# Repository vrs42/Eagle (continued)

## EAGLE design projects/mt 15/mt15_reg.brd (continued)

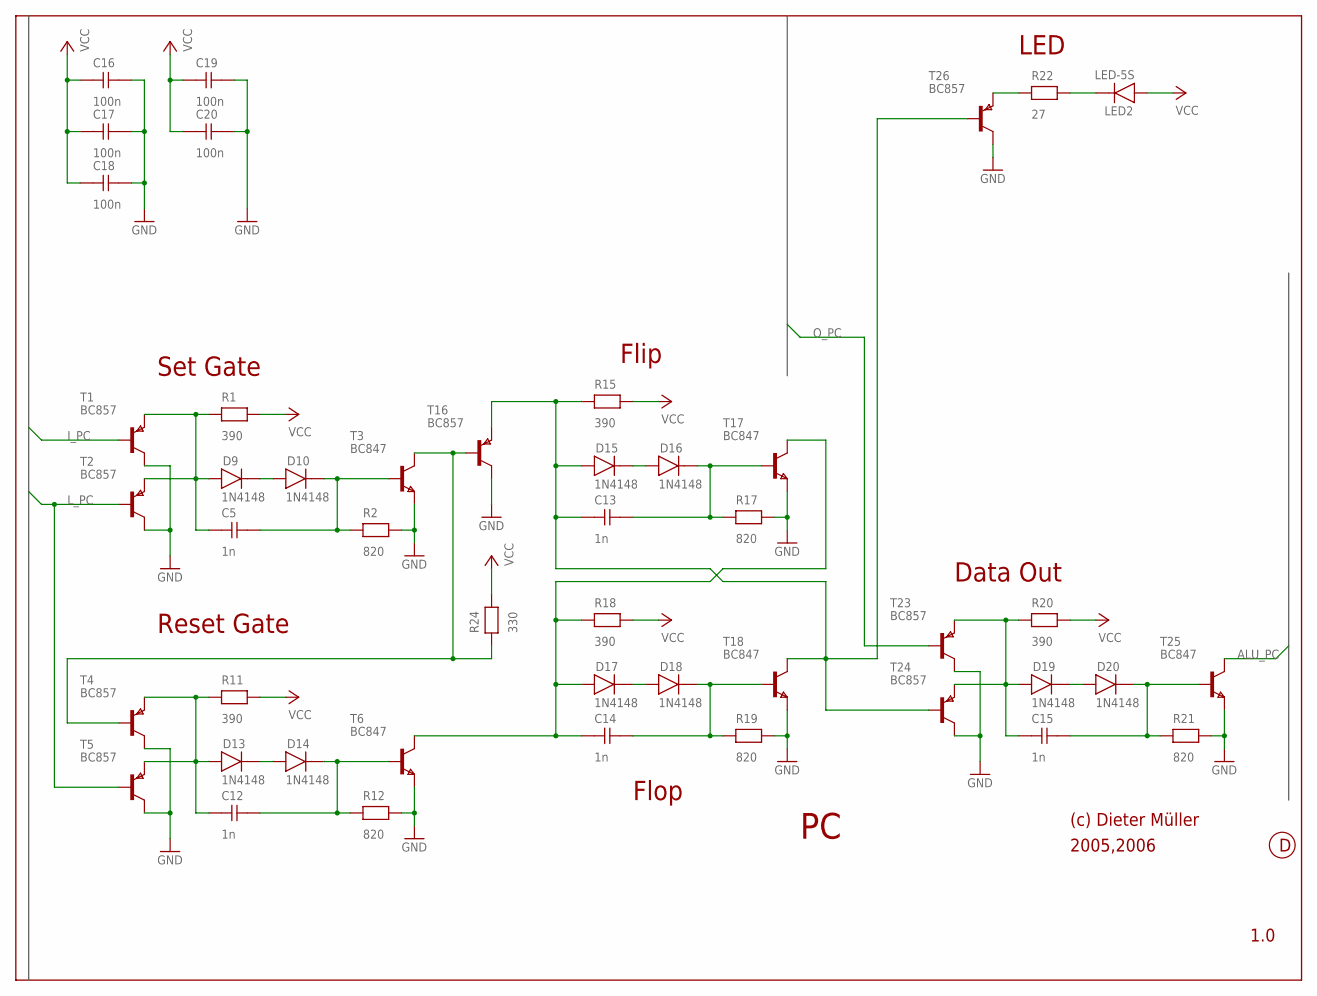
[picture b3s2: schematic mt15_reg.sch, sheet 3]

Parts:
C5, C12, C13, C14, C15: 1n; 0204
C16, C17, C18, C19, C20: 100n; 0204
D9, D10, D13, D14, D15, D16, D17, D18, D19, D20: 1N4148; 0204D
LED2: LED-5S
R1, R11, R15, R18, R20: 390; 0204
R2, R12, R17, R19, R21: 820; 0204
R22: 27; 0204
R24: 330; 0204
T1, T2, T4, T5, T16, T23, T24, T26: BC857; SOT-23
T3, T6, T17, T18, T25: BC847; SOT-23

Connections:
ALU_PC: T25.3 (C)
GND: C16.2, C17.2, C18.2, C19.2, C20.2, R2.2, R12.2, R17.2, R19.2, R21.2, T1.3 (C), T2.3 (C), T3.1 (E), T4.3 (C), T5.3 (C), T6.1 (E), T16.3 (C), T17.1 (E), T18.1 (E), T23.3 (C), T24.3 (C), T25.1 (E), T26.3 (C); also elsewhere on the board
I_PC: T1.2 (B)
L_PC: T2.2 (B), T5.2 (B)
unnamed: C5.1, D9.1 (A), R1.1, T1.1 (E), T2.1 (E)
unnamed: D9.2 (K), D10.1 (A)
unnamed: C5.2, D10.2 (K), R2.1, T3.2 (B)
unnamed: R24.1, T3.3 (C), T4.2 (B), T16.2 (B)
unnamed: C12.1, D13.1 (A), R11.1, T4.1 (E), T5.1 (E)
unnamed: D13.2 (K), D14.1 (A)
unnamed: C12.2, D14.2 (K), R12.1, T6.2 (B)
unnamed: D15.2 (K), D16.1 (A)
unnamed: C13.2, D16.2 (K), R17.1, T17.2 (B)
unnamed: D17.2 (K), D18.1 (A)
unnamed: C14.2, D18.2 (K), R19.1, T18.2 (B)
unnamed: C14.1, D17.1 (A), R18.1, T6.3 (C), T17.3 (C)
unnamed: C13.1, D15.1 (A), R15.1, T16.1 (E), T18.3 (C), T24.2 (B), T26.2 (B)
unnamed: C15.1, D19.1 (A), R20.1, T23.1 (E), T24.1 (E)
unnamed: D19.2 (K), D20.1 (A)
unnamed: C15.2, D20.2 (K), R21.1, T25.2 (B)
unnamed: R22.1, T26.1 (E)
unnamed: LED2.2 (K), R22.2
O_PC: T23.2 (B)
VCC: C16.1, C17.1, C18.1, C19.1, C20.1, LED2.1 (A), R1.2, R11.2, R15.2, R18.2, R20.2, R24.2; also elsewhere on the board

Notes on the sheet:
Set Gate
Reset Gate
Flip
Flop
Data Out
LED
(c) Dieter Müller
2005,2006
1.0

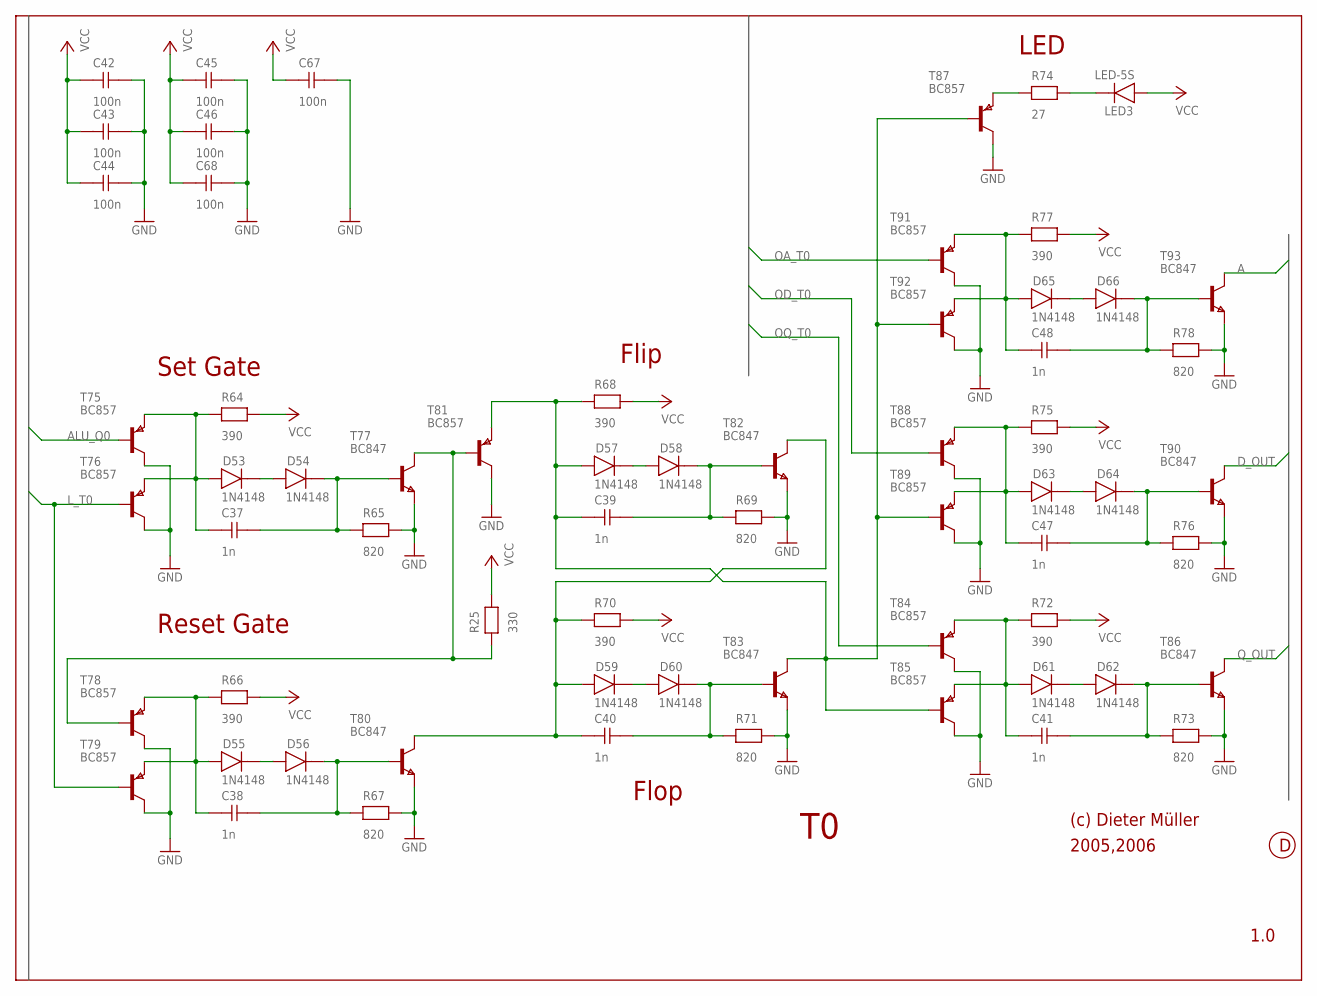
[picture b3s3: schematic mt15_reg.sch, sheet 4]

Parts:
C37, C38, C39, C40, C41, C47, C48: 1n; 0204
C42, C43, C44, C45, C46, C67, C68: 100n; 0204
D53, D54, D55, D56, D57, D58, D59, D60, D61, D62, D63, D64, D65, D66: 1N4148; 0204D
LED3: LED-5S
R25: 330; 0204
R64, R66, R68, R70, R72, R75, R77: 390; 0204
R65, R67, R69, R71, R73, R76, R78: 820; 0204
R74: 27; 0204
T75, T76, T78, T79, T81, T84, T85, T87, T88, T89, T91, T92: BC857; SOT-23
T77, T80, T82, T83, T86, T90, T93: BC847; SOT-23

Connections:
A: T93.3 (C); also elsewhere on the board
ALU_Q0: T75.2 (B)
D_OUT: T90.3 (C); also elsewhere on the board
GND: C42.2, C43.2, C44.2, C45.2, C46.2, C67.2, C68.2, R65.2, R67.2, R69.2, R71.2, R73.2, R76.2, R78.2, T75.3 (C), T76.3 (C), T77.1 (E), T78.3 (C), T79.3 (C), T80.1 (E), T81.3 (C), T82.1 (E), T83.1 (E), T84.3 (C), T85.3 (C), T86.1 (E), T87.3 (C), T88.3 (C), T89.3 (C), T90.1 (E), T91.3 (C), T92.3 (C), T93.1 (E); also elsewhere on the board
L_T0: T76.2 (B), T79.2 (B)
unnamed: C37.1, D53.1 (A), R64.1, T75.1 (E), T76.1 (E)
unnamed: D53.2 (K), D54.1 (A)
unnamed: C37.2, D54.2 (K), R65.1, T77.2 (B)
unnamed: R25.1, T77.3 (C), T78.2 (B), T81.2 (B)
unnamed: C38.1, D55.1 (A), R66.1, T78.1 (E), T79.1 (E)
unnamed: D55.2 (K), D56.1 (A)
unnamed: C38.2, D56.2 (K), R67.1, T80.2 (B)
unnamed: D57.2 (K), D58.1 (A)
unnamed: C39.2, D58.2 (K), R69.1, T82.2 (B)
unnamed: D59.2 (K), D60.1 (A)
unnamed: C40.2, D60.2 (K), R71.1, T83.2 (B)
unnamed: C40.1, D59.1 (A), R70.1, T80.3 (C), T82.3 (C)
unnamed: C39.1, D57.1 (A), R68.1, T81.1 (E), T83.3 (C), T85.2 (B), T87.2 (B), T89.2 (B), T92.2 (B)
unnamed: C41.1, D61.1 (A), R72.1, T84.1 (E), T85.1 (E)
unnamed: D61.2 (K), D62.1 (A)
unnamed: C41.2, D62.2 (K), R73.1, T86.2 (B)
unnamed: R74.1, T87.1 (E)
unnamed: LED3.2 (K), R74.2
unnamed: C47.1, D63.1 (A), R75.1, T88.1 (E), T89.1 (E)
unnamed: D63.2 (K), D64.1 (A)
unnamed: C47.2, D64.2 (K), R76.1, T90.2 (B)
unnamed: C48.1, D65.1 (A), R77.1, T91.1 (E), T92.1 (E)
unnamed: D65.2 (K), D66.1 (A)
unnamed: C48.2, D66.2 (K), R78.1, T93.2 (B)
OA_T0: T91.2 (B)
OD_T0: T88.2 (B)
OQ_T0: T84.2 (B)
Q_OUT: T86.3 (C); also elsewhere on the board
VCC: C42.1, C43.1, C44.1, C45.1, C46.1, C67.1, C68.1, LED3.1 (A), R25.2, R64.2, R66.2, R68.2, R70.2, R72.2, R75.2, R77.2; also elsewhere on the board

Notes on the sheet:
Set Gate
Reset Gate
Flip
Flop
LED
(c) Dieter Müller
2005,2006
1.0

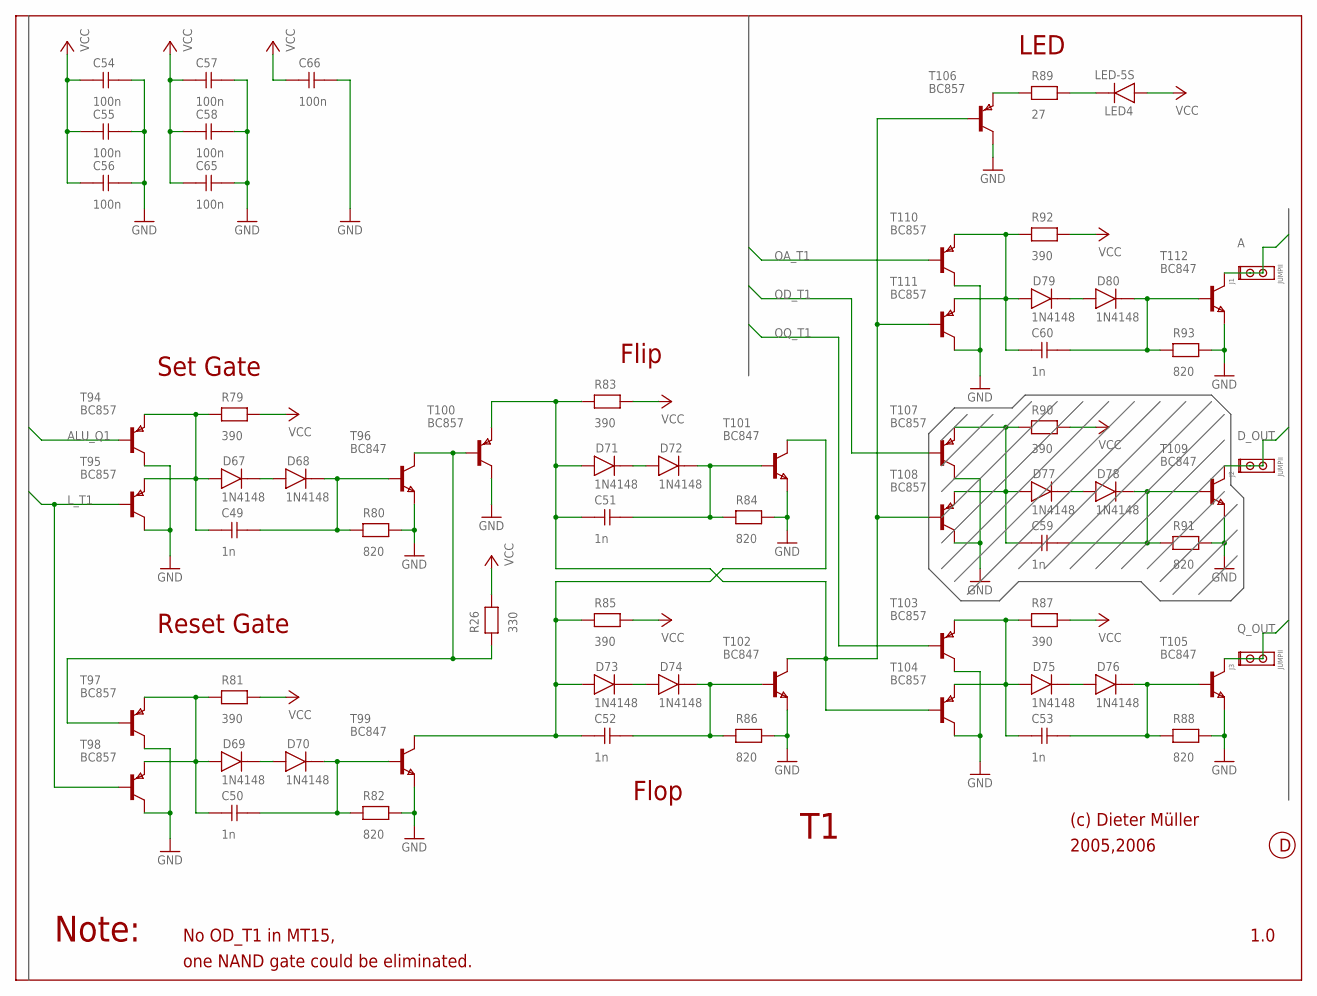
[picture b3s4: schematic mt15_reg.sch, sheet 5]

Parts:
C49, C50, C51, C52, C53, C59, C60: 1n; 0204
C54, C55, C56, C57, C58, C65, C66: 100n; 0204
D67, D68, D69, D70, D71, D72, D73, D74, D75, D76, D77, D78, D79, D80: 1N4148; 0204D
J1, J2, J3: JUMPII
LED4: LED-5S
R26: 330; 0204
R79, R81, R83, R85, R87, R90, R92: 390; 0204
R80, R82, R84, R86, R88, R91, R93: 820; 0204
R89: 27; 0204
T94, T95, T97, T98, T100, T103, T104, T106, T107, T108, T110, T111: BC857; SOT-23
T96, T99, T101, T102, T105, T109, T112: BC847; SOT-23

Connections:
A: J1.1, J1.2, T112.3 (C); also elsewhere on the board
ALU_Q1: T94.2 (B)
D_OUT: J2.1, J2.2, T109.3 (C); also elsewhere on the board
GND: C54.2, C55.2, C56.2, C57.2, C58.2, C65.2, C66.2, R80.2, R82.2, R84.2, R86.2, R88.2, R91.2, R93.2, T94.3 (C), T95.3 (C), T96.1 (E), T97.3 (C), T98.3 (C), T99.1 (E), T100.3 (C), T101.1 (E), T102.1 (E), T103.3 (C), T104.3 (C), T105.1 (E), T106.3 (C), T107.3 (C), T108.3 (C), T109.1 (E), T110.3 (C), T111.3 (C), T112.1 (E); also elsewhere on the board
L_T1: T95.2 (B), T98.2 (B)
unnamed: C49.1, D67.1 (A), R79.1, T94.1 (E), T95.1 (E)
unnamed: D67.2 (K), D68.1 (A)
unnamed: C49.2, D68.2 (K), R80.1, T96.2 (B)
unnamed: R26.1, T96.3 (C), T97.2 (B), T100.2 (B)
unnamed: C50.1, D69.1 (A), R81.1, T97.1 (E), T98.1 (E)
unnamed: D69.2 (K), D70.1 (A)
unnamed: C50.2, D70.2 (K), R82.1, T99.2 (B)
unnamed: D71.2 (K), D72.1 (A)
unnamed: C51.2, D72.2 (K), R84.1, T101.2 (B)
unnamed: D73.2 (K), D74.1 (A)
unnamed: C52.2, D74.2 (K), R86.1, T102.2 (B)
unnamed: C52.1, D73.1 (A), R85.1, T99.3 (C), T101.3 (C)
unnamed: C51.1, D71.1 (A), R83.1, T100.1 (E), T102.3 (C), T104.2 (B), T106.2 (B), T108.2 (B), T111.2 (B)
unnamed: C53.1, D75.1 (A), R87.1, T103.1 (E), T104.1 (E)
unnamed: D75.2 (K), D76.1 (A)
unnamed: C53.2, D76.2 (K), R88.1, T105.2 (B)
unnamed: R89.1, T106.1 (E)
unnamed: LED4.2 (K), R89.2
unnamed: C59.1, D77.1 (A), R90.1, T107.1 (E), T108.1 (E)
unnamed: D77.2 (K), D78.1 (A)
unnamed: C59.2, D78.2 (K), R91.1, T109.2 (B)
unnamed: C60.1, D79.1 (A), R92.1, T110.1 (E), T111.1 (E)
unnamed: D79.2 (K), D80.1 (A)
unnamed: C60.2, D80.2 (K), R93.1, T112.2 (B)
OA_T1: T110.2 (B)
OD_T1: T107.2 (B)
OQ_T1: T103.2 (B)
Q_OUT: J3.1, J3.2, T105.3 (C); also elsewhere on the board
VCC: C54.1, C55.1, C56.1, C57.1, C58.1, C65.1, C66.1, LED4.1 (A), R26.2, R79.2, R81.2, R83.2, R85.2, R87.2, R90.2, R92.2; also elsewhere on the board

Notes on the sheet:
Set Gate
Reset Gate
Flip
Flop
LED
(c) Dieter Müller
2005,2006
1.0
Note:
No OD_T1 in MT15,
one NAND gate could be eliminated.

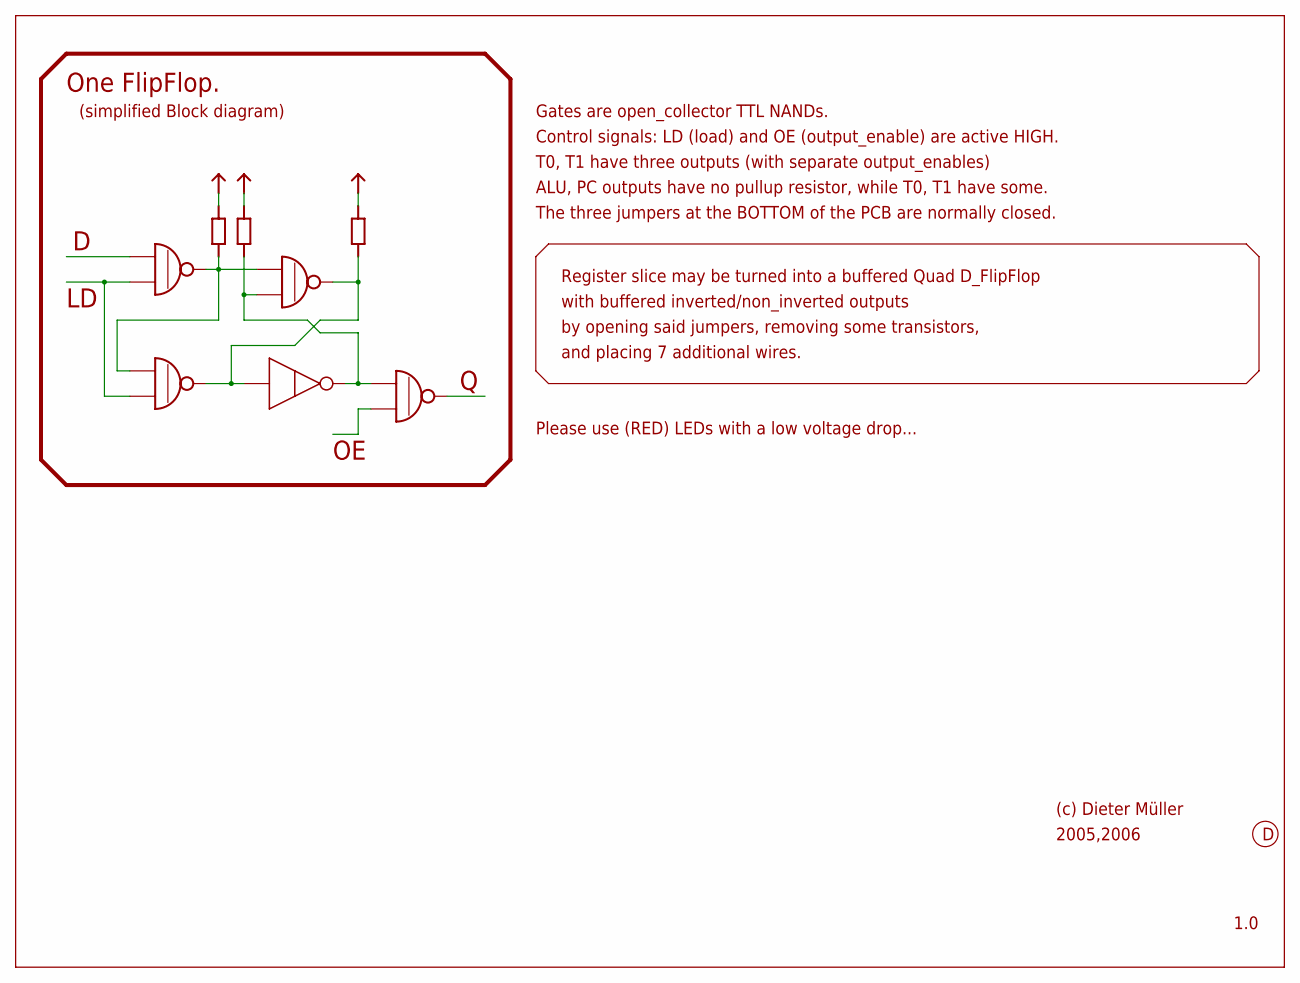
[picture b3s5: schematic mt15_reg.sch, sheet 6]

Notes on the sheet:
(c) Dieter Müller
2005,2006
1.0
One FlipFlop.
(simplified Block diagram)
Gates are open_collector TTL NANDs.
T0, T1 have three outputs (with separate output_enables)
ALU, PC outputs have no pullup resistor, while T0, T1 have some.
The three jumpers at the BOTTOM of the PCB are normally closed.
Control signals: LD (load) and OE (output_enable) are active HIGH.
Register slice may be turned into a buffered Quad D_FlipFlop
with buffered inverted/non_inverted outputs
by opening said jumpers, removing some transistors,
and placing 7 additional wires.
Please use (RED) LEDs with a low voltage drop...

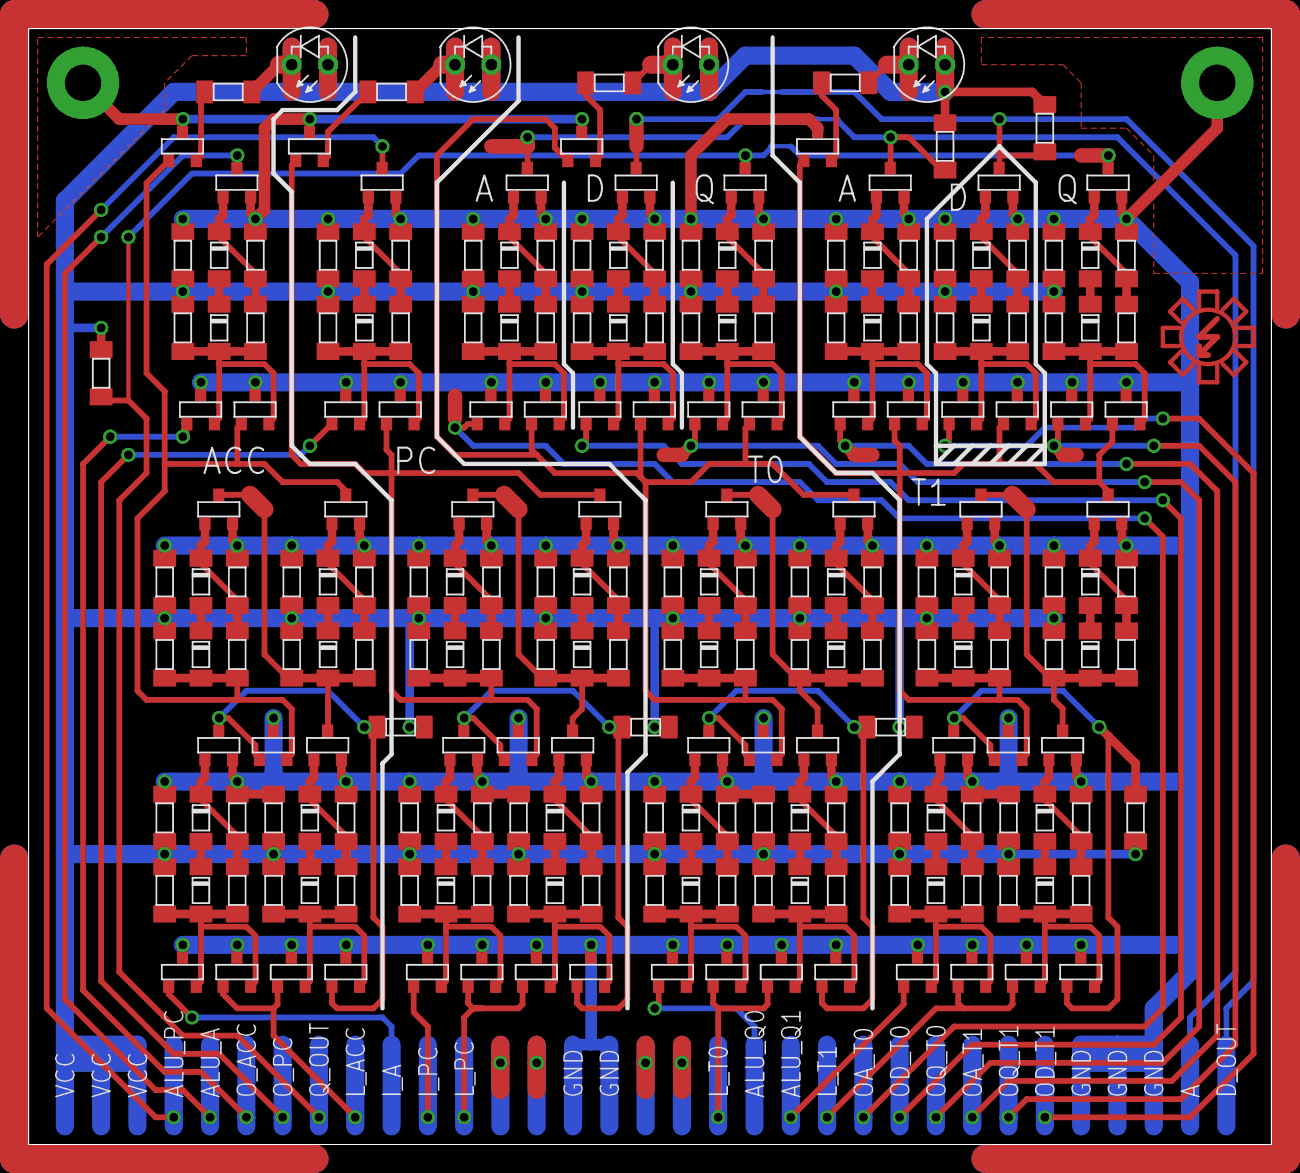
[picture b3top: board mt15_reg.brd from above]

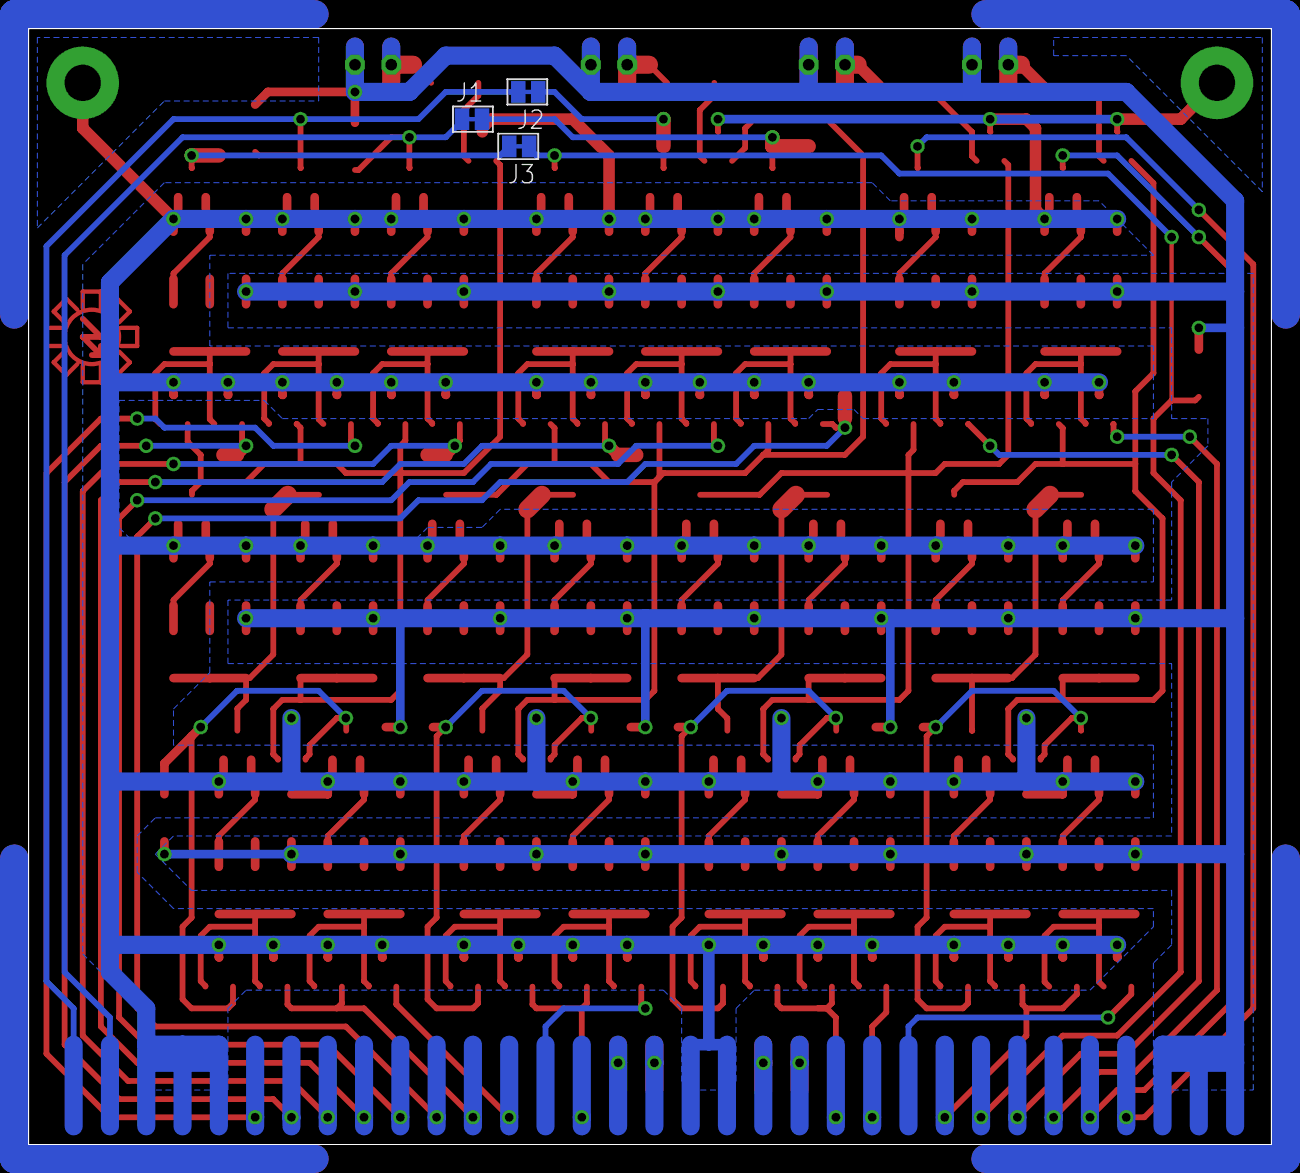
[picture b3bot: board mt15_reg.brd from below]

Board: 2 copper layers, 87.0 x 78.1 mm, 227 parts (3 on the bottom side), 93 nets.

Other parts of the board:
U$46: T1

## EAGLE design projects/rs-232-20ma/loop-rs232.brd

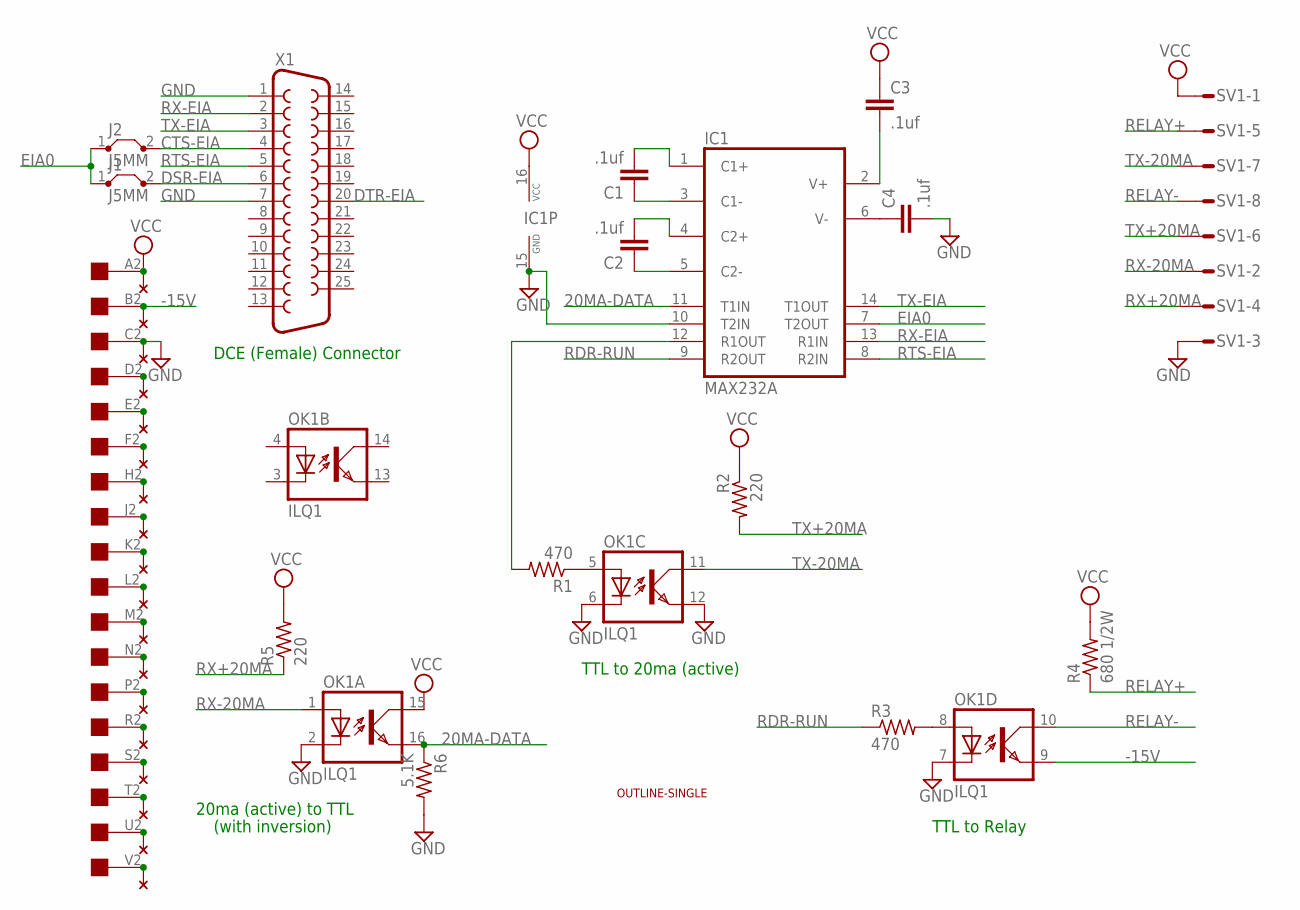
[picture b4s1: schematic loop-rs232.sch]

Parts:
C1, C2, C3, C4: .1uf; C050-025X075
IC1: MAX232A; DIL16
J1, J2: J5MM; 05
OK1: ILQ1; DIL16
R1, R3: 470; 0207/10
R2, R5: 220; 0207/10
R4: 680 1/2W; 0207/10
R6: 5.1K; 0207/10
SV1: S08P
U$2: EDGE-1; EDGE-CON1
U$3: OUTLINE-SINGLE; SINGLE
U$4: THRU-HOLE1
X1: F25H

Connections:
20MA-DATA: IC1.11 (T1IN), OK1.16 (EMIT), R6.1
-15V: OK1.9 (EMIT), U$2.B2, U$4.B2
CTS-EIA: J2.2, X1.4
DSR-EIA: J1.2, X1.6
DTR-EIA: X1.20
EIA0: IC1.7 (T2OUT), J1.1, J2.1
EIA-DATA: OK1.5 (A), R1.1
GND: C4.2, IC1.10 (T2IN), IC1.15 (GND), OK1.2 (C), OK1.6 (C), OK1.7 (C), OK1.12 (EMIT), R6.2, SV1.3, U$2.C2, U$4.C2, X1.1, X1.7
unnamed: C2.1, IC1.5 (C2-)
unnamed: C2.2, IC1.4 (C2+)
unnamed: C1.2, IC1.1 (C1+)
unnamed: C1.1, IC1.3 (C1-)
unnamed: U$2.V2, U$4.V2
unnamed: U$2.U2, U$4.U2
unnamed: U$2.T2, U$4.T2
unnamed: IC1.12 (R1OUT), R1.2
unnamed: C3.2, IC1.2 (V+)
unnamed: C4.1, IC1.6 (V-)
unnamed: U$2.S2, U$4.S2
unnamed: OK1.8 (A), R3.2
unnamed: U$2.R2, U$4.R2
unnamed: U$2.P2, U$4.P2
unnamed: U$2.N2, U$4.N2
unnamed: U$2.M2, U$4.M2
unnamed: U$2.L2, U$4.L2
unnamed: U$2.K2, U$4.K2
unnamed: U$2.J2, U$4.J2
unnamed: U$2.H2, U$4.H2
unnamed: U$2.F2, U$4.F2
unnamed: U$2.E2, U$4.E2
unnamed: U$2.D2, U$4.D2
RDR-RUN: IC1.9 (R2OUT), R3.1
RELAY+: R4.1, SV1.5
RELAY-: OK1.10 (COL), SV1.8
RTS-EIA: IC1.8 (R2IN), X1.5
RX+20MA: R5.1, SV1.4
RX-20MA: OK1.1 (A), SV1.2
RX-EIA: IC1.13 (R1IN), X1.2
TX+20MA: R2.2, SV1.6
TX-20MA: OK1.11 (COL), SV1.7
TX-EIA: IC1.14 (T1OUT), X1.3
VCC: C3.1, IC1.16 (VCC), OK1.15 (COL), R2.1, R4.2, R5.2, SV1.1, U$2.A2, U$4.A2

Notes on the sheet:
20ma (active) to TTL
TTL to 20ma (active)
DCE (Female) Connector
TTL to Relay
(with inversion)

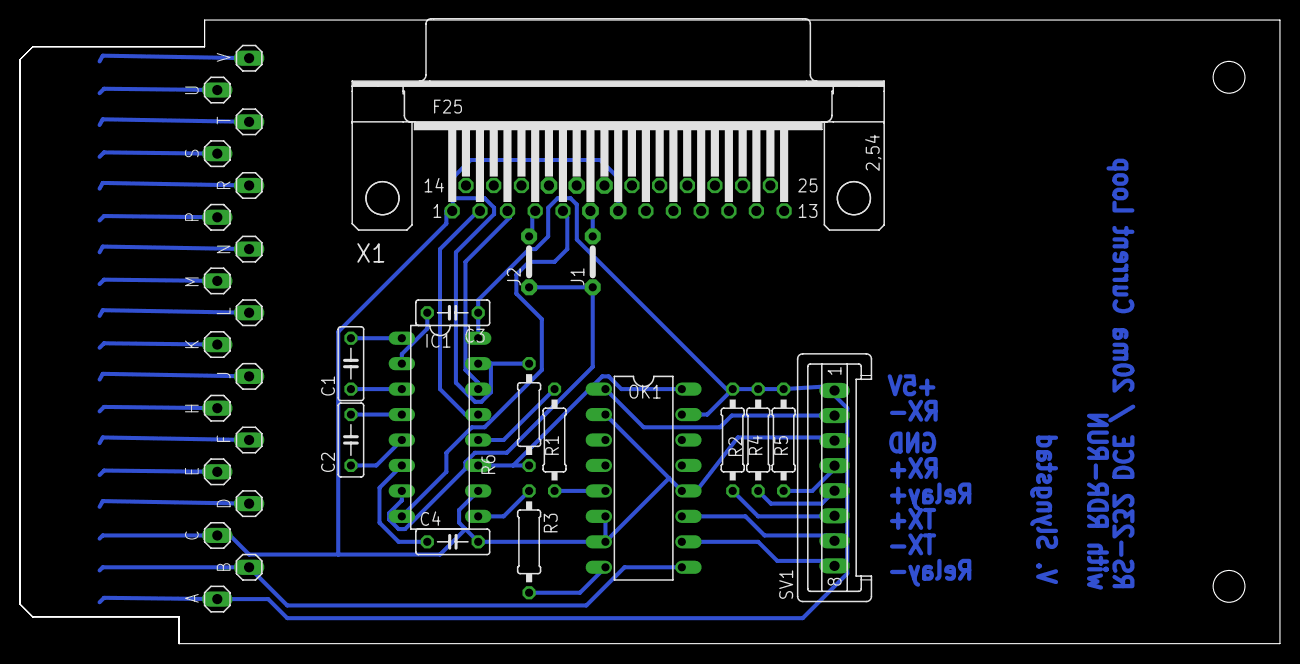
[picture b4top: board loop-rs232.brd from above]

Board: 2 copper layers, 125.7 x 62.2 mm, 19 parts (0 on the bottom side), 41 nets.

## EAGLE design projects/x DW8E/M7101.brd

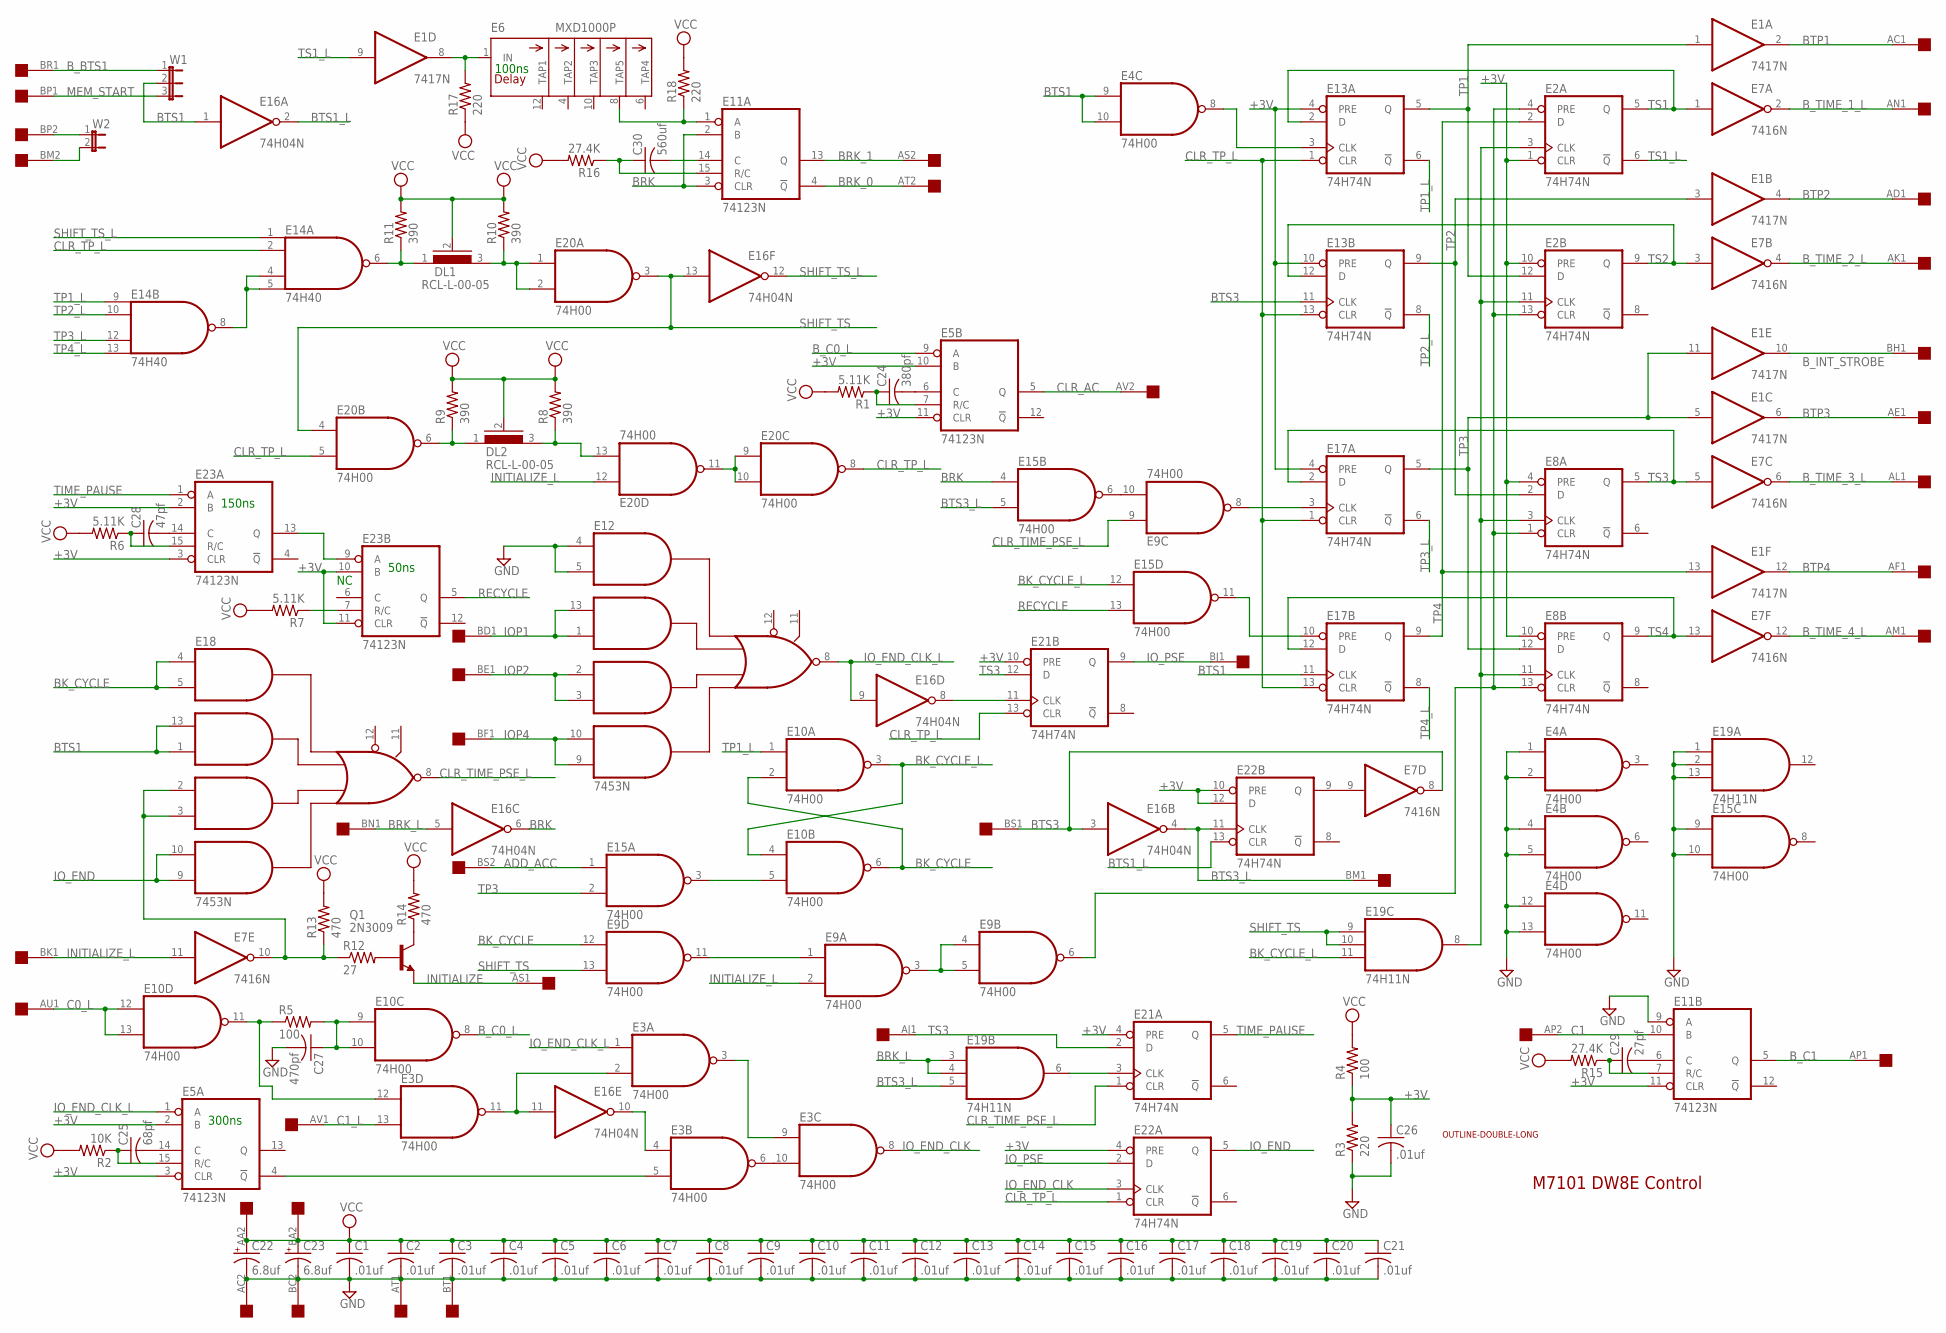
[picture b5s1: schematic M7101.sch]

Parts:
C1, C2, C3, C4, C5, C6, C7, C8, C9, C10, C11, C12, C13, C14, C15, C16, C17, C18, C19, C20, C21, C26: .01uf; C050-025X075
C22, C23: 6.8uf; E22-6
C24: 380pf; C050-025X075
C25: 68pf; C050-025X075
C27: 470pf; C050-025X075
C28: 47pf; C050-025X075
C29: 27pf; C050-025X075
C30: 560uf; C050-025X075
DL1, DL2: RCL-L-00-05
E1: 7417N; DIL14
E2, E8, E13, E17, E21, E22: 74H74N; DIL14
E3, E4, E9, E10, E15, E20: 74H00; DIL14
E5, E11, E23: 74123N; DIL16
E6: MXD1000P; DIL14
E7: 7416N; DIL14
E12, E18: 7453N; DIL14
E14: 74H40; DIL14
E16: 74H04N; DIL14
E19: 74H11N; DIL14
EDGE: DOUBLE; EDGE-CON4
Q1: 2N3009; TO18
R1, R6, R7: 5.11K; 0207/10
R2: 10K; 0207/10
R3, R17, R18: 220; 0207/10
R4, R5: 100; 0207/10
R8, R9, R10, R11: 390; 0207/10
R12: 27; 0207/10
R13, R14: 470; 0207/10
R15, R16: 27.4K; 0207/10
U$1: OUTLINE-DOUBLE-LONG; DOUBLE-LONG
W1: JP2E; JP2
W2: JP1E; JP1

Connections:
+3V: C26.1, E2.1 (CLR), E2.10 (PRE), E5.2 (B), E5.3 (CLR), E5.10 (B), E5.11 (CLR), E8.4 (PRE), E8.10 (PRE), E11.11 (CLR), E13.4 (PRE), E13.10 (PRE), E17.4 (PRE), E21.4 (PRE), E21.10 (PRE), E22.4 (PRE), E22.10 (PRE), E22.12 (D), E23.2 (B), E23.3 (CLR), E23.10 (B), E23.11 (CLR), R3.2, R4.1
ADD_ACC: E15.1 (I0), EDGE.BS2
BK_CYCLE: E9.12 (I0), E10.2 (I1), E10.6 (O), E18.4 (I1), E18.5 (I2)
BK_CYCLE_L: E10.3 (O), E10.4 (I0), E15.12 (I0), E19.11 (I2)
BRK: E11.2 (B), E11.3 (CLR), E15.4 (I0), E16.6 (O)
BRK_0: E11.4 (!Q), EDGE.AT2
BRK_1: E11.13 (Q), EDGE.AS2
BRK_L: E16.5 (I), E19.3 (I0), E19.4 (I1), EDGE.BN1
BTP1: E1.2 (O), EDGE.AC1
BTP2: E1.4 (O), EDGE.AD1
BTP3: E1.6 (O), EDGE.AE1
BTP4: E1.12 (O), EDGE.AF1
BTS1: E4.9 (I0), E4.10 (I1), E16.1 (I), E17.11 (CLK), E18.1 (I4), E18.13 (I3), W1.2
BTS1_L: E16.2 (O), E22.13 (CLR)
BTS3: E7.8 (O), E13.11 (CLK), E16.3 (I), EDGE.BS1
BTS3_L: E15.5 (I1), E16.4 (O), E19.5 (I2), E22.11 (CLK), EDGE.BM1
B_BTS1: EDGE.BR1, W1.1
B_C0_L: E5.9 (A), E10.8 (O)
B_C1: E11.5 (Q), EDGE.AP1
B_INT_STROBE: E1.10 (O), EDGE.BH1
B_TIME_1_L: E7.2 (O), EDGE.AN1
B_TIME_2_L: E7.4 (O), EDGE.AK1
B_TIME_3_L: E7.6 (O), EDGE.AL1
B_TIME_4_L: E7.12 (O), EDGE.AM1
C0_L: E10.12 (I0), E10.13 (I1), EDGE.AU1
C1: E11.10 (B), EDGE.AP2
C1_L: E3.13 (I1), EDGE.AV1
CLR_AC: E5.5 (Q), EDGE.AV2
CLR_TIME_PSE_L: E9.9 (I0), E18.8 (O), E21.1 (CLR)
CLR_TP_L: E13.1 (CLR), E13.13 (CLR), E14.2 (I1), E17.1 (CLR), E17.13 (CLR), E20.5 (I1), E20.8 (O), E21.13 (CLR), E22.1 (CLR)
GND: C1.2, C2.2, C3.2, C4.2, C5.2, C6.2, C7.2, C8.2, C9.2, C10.2, C11.2, C12.2, C13.2, C14.2, C15.2, C16.2, C17.2, C18.2, C19.2, C20.2, C21.2, C22.-, C23.-, C26.2, C27.2, E1.7 (GND), E2.7 (GND), E3.7 (GND), E4.1 (I0), E4.2 (I1), E4.4 (I0), E4.5 (I1), E4.7 (GND), E4.12 (I0), E4.13 (I1), E5.8 (GND), E6.7 (GND), E7.7 (GND), E8.7 (GND), E9.7 (GND), E10.7 (GND), E11.8 (GND), E11.9 (A), E12.4 (I1), E12.5 (I2), E12.7 (GND), E13.7 (GND), E14.7 (GND), E15.7 (GND), E15.9 (I0), E15.10 (I1), E16.7 (GND), E17.7 (GND), E18.7 (GND), E19.1 (I0), E19.2 (I1), E19.7 (GND), E19.13 (I2), E20.7 (GND), E21.7 (GND), E22.7 (GND), E23.8 (GND), EDGE.AC2, EDGE.AT1, EDGE.BC2, EDGE.BT1, R3.1
INIT: E7.10 (O), E18.2 (I5), E18.3 (I6), R12.1, R13.1
INITIALIZE: EDGE.AS1, Q1.1 (E)
INITIALIZE_L: E7.11 (I), E9.2 (I1), E20.12 (I0), EDGE.BK1
IOP1: E12.1 (I4), E12.13 (I3), EDGE.BD1
IOP2: E12.2 (I5), E12.3 (I6), EDGE.BE1
IOP4: E12.9 (I8), E12.10 (I7), EDGE.BF1
IO_END: E18.9 (I8), E18.10 (I7), E22.5 (Q)
IO_END_CLK: E3.8 (O), E22.3 (CLK)
IO_END_CLK_L: E3.1 (I0), E5.1 (A), E12.8 (O), E16.9 (I)
IO_PSE: E21.9 (Q), E22.2 (D), EDGE.BJ1
MEM_START: EDGE.BP1, W1.3
unnamed: E6.8 (TAP5), E11.1 (A), R18.1
unnamed: E1.8 (O), E6.1 (IN), R17.2
unnamed: C30.1, E11.15 (R/C), R16.1
unnamed: C30.2, E11.14 (C)
unnamed: E9.8 (O), E17.3 (CLK)
unnamed: E14.4 (I2), E14.5 (I3), E14.8 (O)
unnamed: DL1.1, E14.6 (O), R11.1
unnamed: DL1.3, E20.1 (I0), E20.2 (I1), R10.1
unnamed: DL2.1, E20.6 (O), R9.1
unnamed: DL2.3, E20.13 (I1), R8.1
unnamed: E20.9 (I0), E20.10 (I1), E20.11 (O)
unnamed: C28.2, E23.14 (C)
unnamed: C28.1, E23.15 (R/C), R6.1
unnamed: E23.9 (A), E23.13 (Q)
unnamed: E23.7 (R/C), R7.1
unnamed: Q1.2 (B), R12.2
unnamed: Q1.3 (C), R14.1
unnamed: E3.12 (I0), E10.11 (O), R5.1
unnamed: C27.1, E10.9 (I0), E10.10 (I1), R5.2
unnamed: C25.2, E5.14 (C)
unnamed: C25.1, E5.15 (R/C), R2.1
unnamed: E3.5 (I1), E5.4 (!Q)
unnamed: E3.4 (I0), E16.10 (O)
unnamed: E3.2 (I1), E3.11 (O), E16.11 (I)
unnamed: E3.6 (O), E3.10 (I1)
unnamed: E3.3 (O), E3.9 (I0)
unnamed: E16.8 (O), E21.11 (CLK)
unnamed: E10.5 (I1), E15.3 (O)
unnamed: E9.1 (I0), E9.11 (O)
unnamed: E9.3 (O), E9.4 (I0), E9.5 (I1)
unnamed: C29.2, E11.6 (C)
unnamed: C29.1, E11.7 (R/C), R15.1
unnamed: E9.10 (I1), E15.6 (O)
unnamed: E4.8 (O), E13.3 (CLK)
unnamed: E2.4 (PRE), E2.13 (CLR), E8.1 (CLR), E8.13 (CLR), E9.6 (O)
unnamed: E19.6 (O), E21.3 (CLK)
unnamed: C24.2, E5.6 (C)
unnamed: C24.1, E5.7 (R/C), R1.1
unnamed: E7.9 (I), E22.9 (Q)
unnamed: E15.11 (O), E17.10 (PRE)
unnamed: EDGE.BP2, W2.1
unnamed: E2.3 (CLK), E2.11 (CLK), E8.3 (CLK), E8.11 (CLK), E19.8 (O)
unnamed: EDGE.BM2, W2.2
RECYCLE: E15.13 (I1), E23.5 (Q)
SHIFT_TS: E9.13 (I1), E16.13 (I), E19.9 (I0), E19.10 (I1), E20.3 (O), E20.4 (I0)
SHIFT_TS_L: E14.1 (I0), E16.12 (O)
TIME_PAUSE: E21.5 (Q), E23.1 (A)
TP1: E1.1 (I), E2.12 (D), E13.5 (Q)
TP1_L: E10.1 (I0), E13.6 (!Q), E14.9 (I0)
TP2: E1.3 (I), E8.2 (D), E13.9 (Q)
TP2_L: E13.8 (!Q), E14.10 (I1)
TP3: E1.5 (I), E1.11 (I), E8.12 (D), E15.2 (I1), E17.5 (Q)
TP3_L: E14.12 (I2), E17.6 (!Q)
TP4: E1.13 (I), E2.2 (D), E17.9 (Q)
TP4_L: E14.13 (I3), E17.8 (!Q)
TS1: E2.5 (Q), E7.1 (I), E13.2 (D)
TS1_L: E1.9 (I), E2.6 (!Q)
TS2: E2.9 (Q), E7.3 (I), E13.12 (D)
TS3: E7.5 (I), E8.5 (Q), E17.2 (D), E21.2 (D), E21.12 (D), EDGE.AJ1
TS4: E7.13 (I), E8.9 (Q), E17.12 (D)
VCC: C1.1, C2.1, C3.1, C4.1, C5.1, C6.1, C7.1, C8.1, C9.1, C10.1, C11.1, C12.1, C13.1, C14.1, C15.1, C16.1, C17.1, C18.1, C19.1, C20.1, C21.1, C22.+, C23.+, DL1.2, DL2.2, E1.14 (VCC), E2.14 (VCC), E3.14 (VCC), E4.14 (VCC), E5.16 (VCC), E6.14 (VCC), E7.14 (VCC), E8.14 (VCC), E9.14 (VCC), E10.14 (VCC), E11.16 (VCC), E12.14 (VCC), E13.14 (VCC), E14.14 (VCC), E15.14 (VCC), E16.14 (VCC), E17.14 (VCC), E18.14 (VCC), E19.14 (VCC), E20.14 (VCC), E21.14 (VCC), E22.14 (VCC), E23.16 (VCC), EDGE.AA2, EDGE.BA2, R1.2, R2.2, R4.2, R6.2, R7.2, R8.2, R9.2, R10.2, R11.2, R13.2, R14.2, R15.2, R16.2, R17.1, R18.2

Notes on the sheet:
100ns
300ns
150ns
50ns
M7101 DW8E Control
